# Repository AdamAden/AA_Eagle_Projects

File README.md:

# AA_Eagle_Projects
PCB design in Eagle
<ul> 
<li>Jeremy Blum Tutorials</li>
<li>SparkFun Tutorials</li>

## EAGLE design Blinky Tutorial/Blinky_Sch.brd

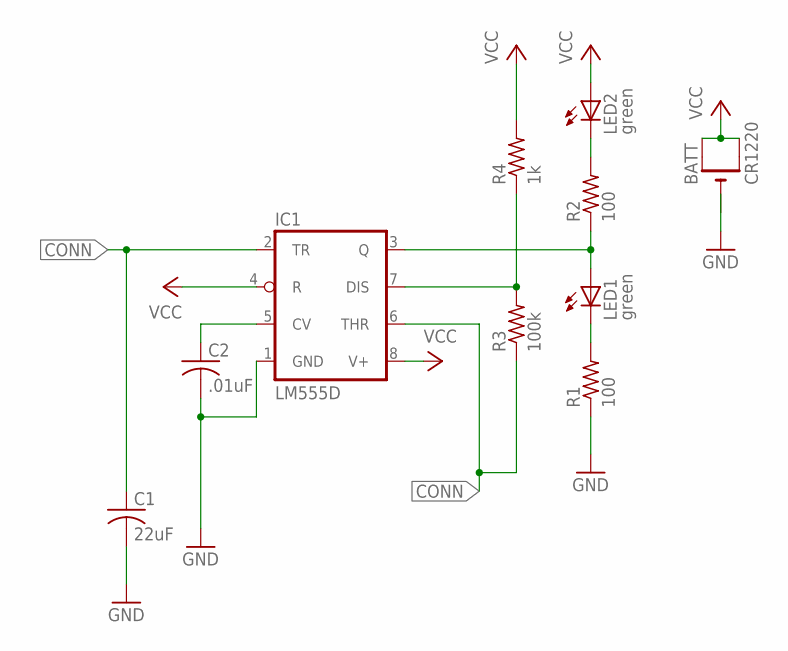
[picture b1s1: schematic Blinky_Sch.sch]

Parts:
BATT: CR1220; CR1220-SMD; MPN 3080
C1: 22uF; C0805
C2: .01uF; C0805
IC1: LM555D; SO08
LED1, LED2: green; CHIPLED_0805
R1, R2: 100; R0805
R3: 100k; R0805
R4: 1k; R0805

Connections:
CONN: C1.1, IC1.2 (TR), IC1.6 (THR), R3.1
GND: C1.2, C2.2, IC1.1 (GND), R1.1
unnamed: LED2.C, R2.2
unnamed: IC1.3 (Q), LED1.A, R2.1
unnamed: LED1.C, R1.2
unnamed: IC1.7 (DIS), R3.2, R4.1
unnamed: C2.1, IC1.5 (CV)
VCC: BATT.+$1 (+), BATT.+$2 (+1), IC1.4 (R), IC1.8 (V+), LED2.A, R4.2

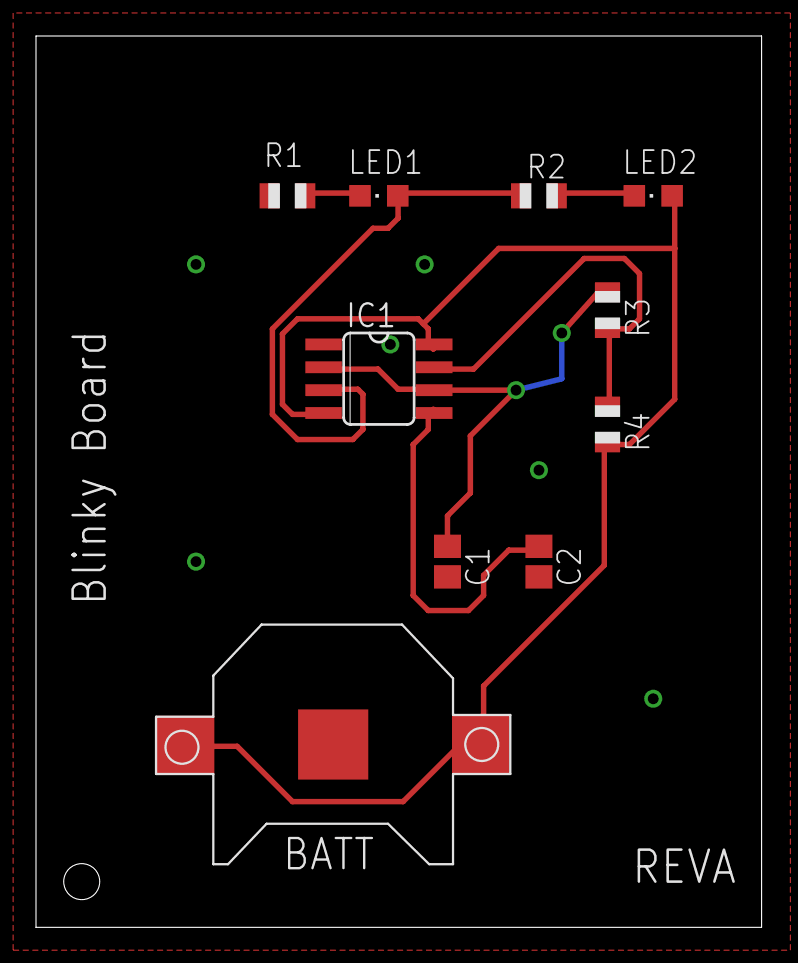
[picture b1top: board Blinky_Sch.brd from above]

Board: 2 copper layers, 40.3 x 49.5 mm, 10 parts (0 on the bottom side), 8 nets.

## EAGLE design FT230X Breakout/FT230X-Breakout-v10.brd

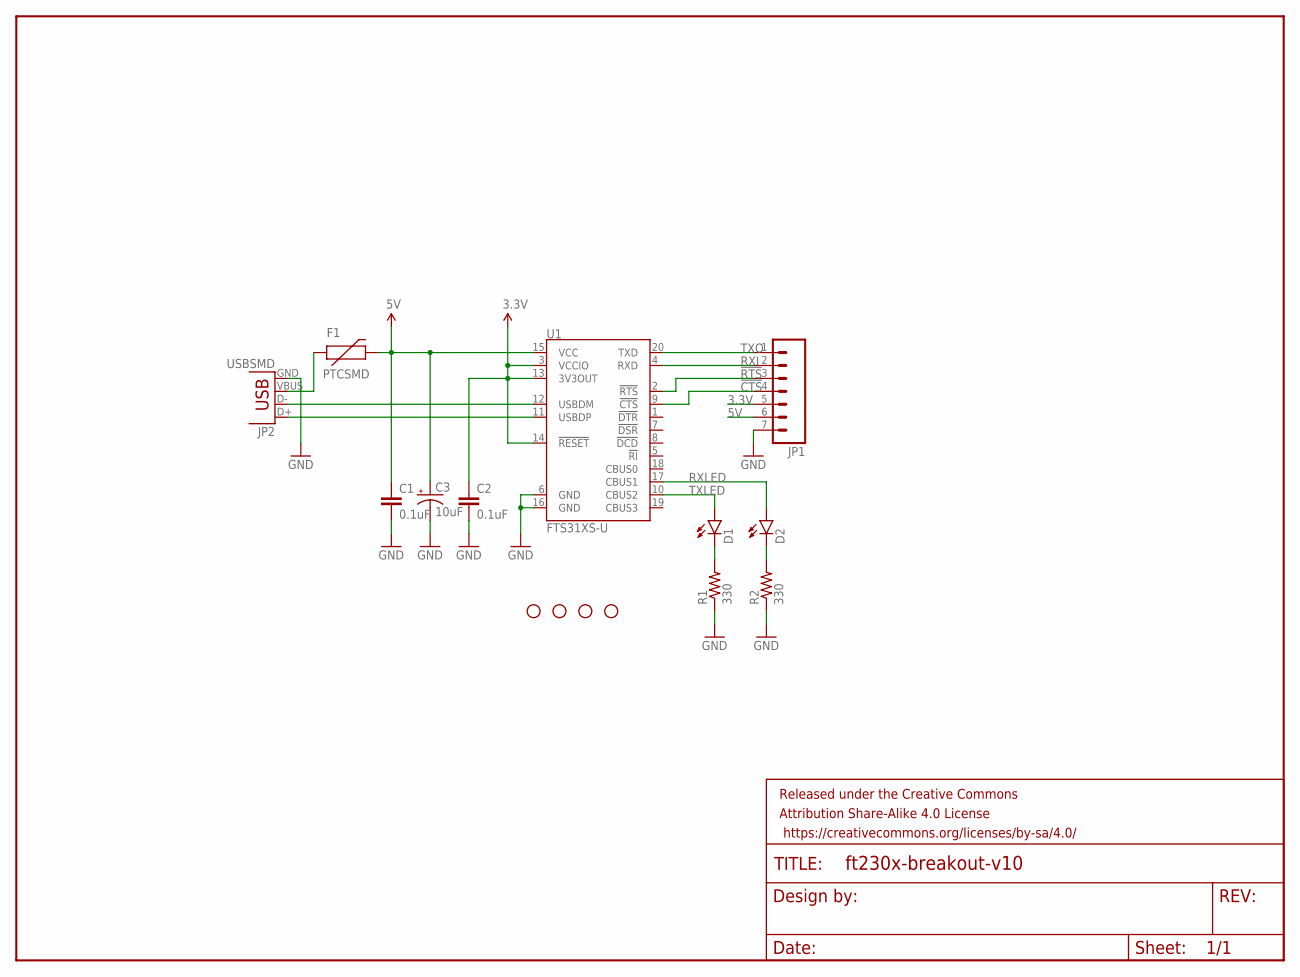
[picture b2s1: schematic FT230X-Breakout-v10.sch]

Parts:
C1, C2: 0.1uF; 0603-CAP
C3: 10uF; EIA3216-KIT
D1, D2: LED0603; LED-0603
F1: PTCSMD; PTC-1206
FRAME1: FRAME-LETTER; CREATIVE_COMMONS
JP1: M07; 1X07
JP2: USBSMD; USB-MINIB
R1, R2: 330; 0603-RES
STANDOFF1, STANDOFF2, STANDOFF3, STANDOFF4: STAND-OFF
U1: FTS31XS-U; SSOP20_L

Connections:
3.3V: C2.1, JP1.5, U1.3 (VCCIO), U1.13 (3V3OUT), U1.14 (!RESET)
5V: C1.1, C3.A (+), F1.2, JP1.6, U1.15 (VCC)
!CTS: JP1.4, U1.9 (!CTS)
!RTS: JP1.3, U1.2 (!RTS)
GND: C1.2, C2.2, C3.C (-), JP1.7, JP2.GND, R1.1, R2.1, U1.6 (GND), U1.16 (GND)
unnamed: JP2.D-, U1.12 (USBDM)
unnamed: F1.1, JP2.VBUS
unnamed: JP2.D+, U1.11 (USBDP)
unnamed: D1.C, R1.2
unnamed: D2.C, R2.2
RXI: JP1.2, U1.4 (RXD)
RXLED: D2.A, U1.17 (CBUS1)
TXLED: D1.A, U1.10 (CBUS2)
TXO: JP1.1, U1.20 (TXD)

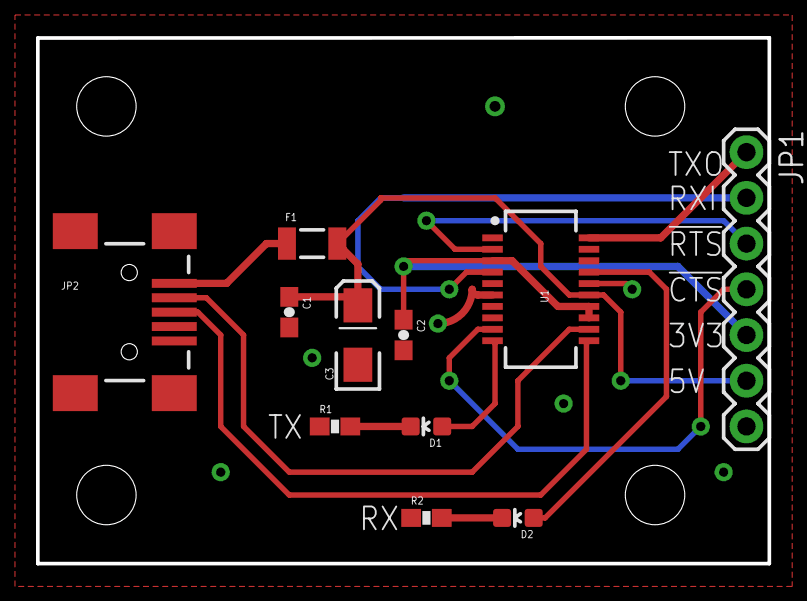
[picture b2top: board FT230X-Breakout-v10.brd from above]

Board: 2 copper layers, 40.6 x 29.2 mm, 16 parts (0 on the bottom side), 14 nets.

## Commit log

2015-11-19 Updated to include details about tutorials

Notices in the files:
parts and their libraries:
SparkFun-Passives: Licensing: Creative Commons ShareAlike 4.0 International - https://creativecommons.org/licenses/by-sa/4.0
SparkFun-Aesthetics: Released under the Creative Commons Attribution Share-Alike 4.0 License
SparkFun-Aesthetics: https://creativecommons.org/licenses/by-sa/4.0
